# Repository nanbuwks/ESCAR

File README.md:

# ESCAR

ESP8266 IoT prototype board.

function:

- LEGO block 8 x 4 knoch size
- DC motor driver x 2
- Universal Area
- 5V to 3.3V regulator
- Full color LED
- Serial connector

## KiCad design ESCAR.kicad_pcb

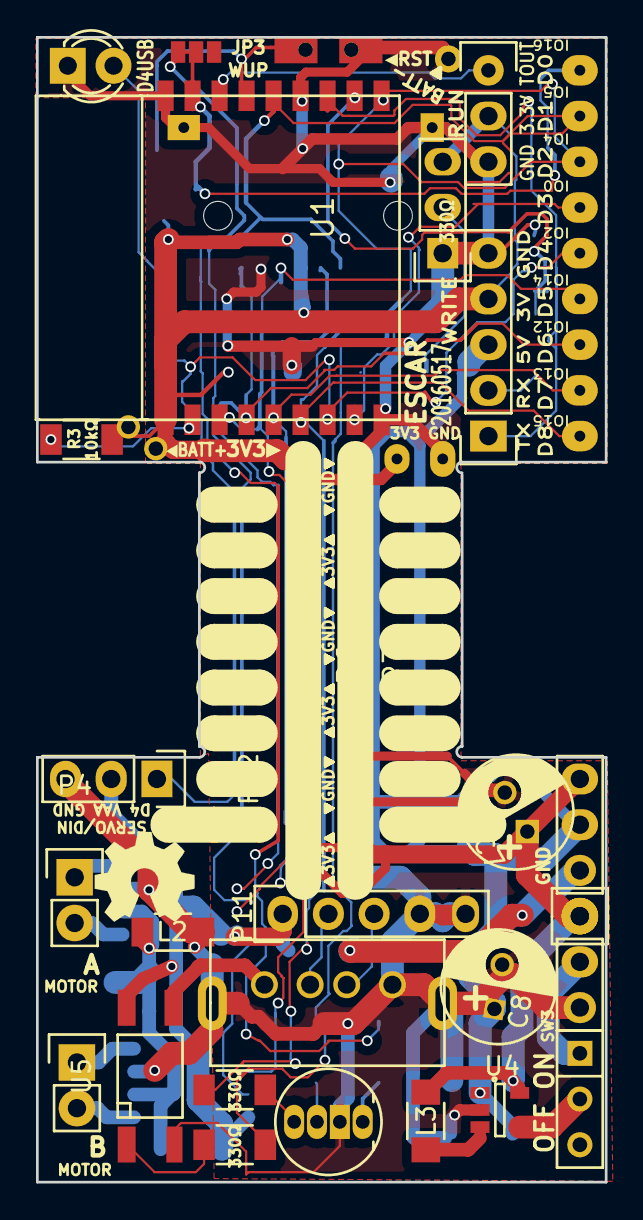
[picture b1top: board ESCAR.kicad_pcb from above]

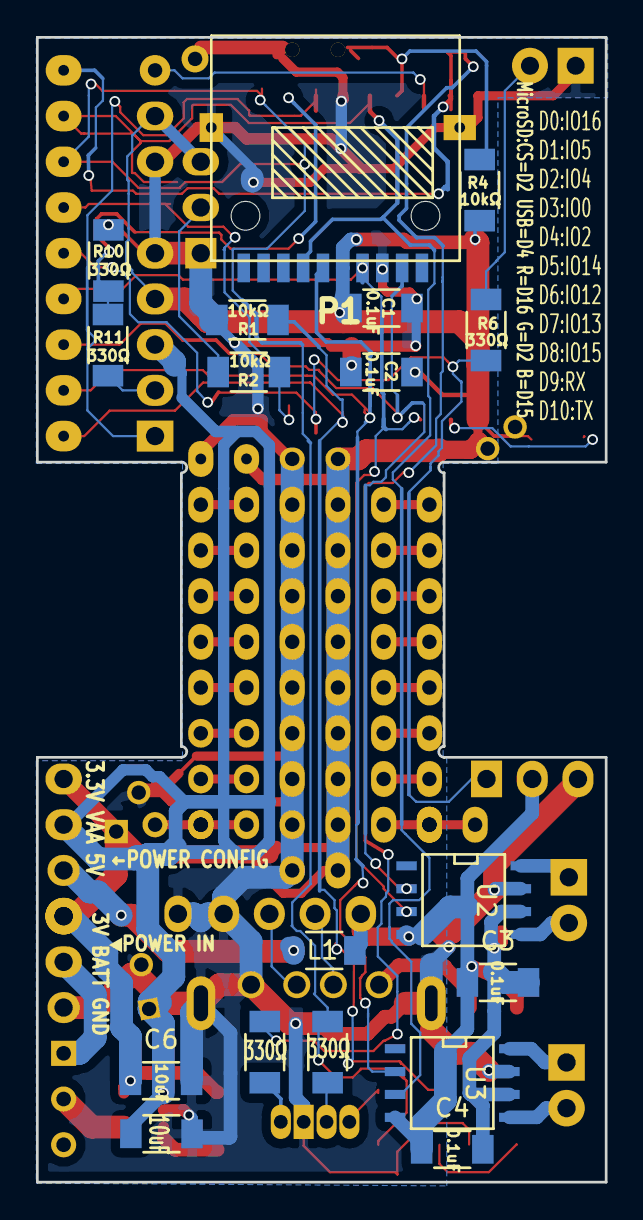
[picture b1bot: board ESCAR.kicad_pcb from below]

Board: 2 copper layers, 31.6 x 63.6 mm, 69 parts (36 on the bottom side), 37 nets.

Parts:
C1, C2, C3, C4: 0.1uF; C_1206_HandSoldering_Small
C5, C6: 10uF; C_1206_HandSoldering_Small
C7, C8: 100uF; C_Radial_D6.3_L11.2_P2.5
D1: YELLOW; LED-3MM
D2: LED_RCBG; LED-RGB-5MM_Common_Cathode
JP1: MODE_JP; Pin_Header_Straight_1x03
JP2: WAKEUP; Solder_Jumper_3
JP4: POWER_JUMPER; Pin_Header_Straight_1x04
L1, L2: INDUCTOR_SMALL; C_1206_HandSoldering_Small
L3: 4.7uH; C_1206_HandSoldering_Small
OSHW: 1.1; OSHW_LOGL_SYLK_5mm
P1: MICRO_SD; TF_Socket_DONGGUAN_MINYUE_ELECTRONICS
P2: BREADBOARD; SolderWirePad_Oval_9xInline_0-6mmDrill
P3: PROGRAM; Pin_Header_Straight_1x05
P4: MOTOR_A; Pin_Header_Straight_1x02
P5: MOTOR_B; Pin_Header_Straight_1x02
P6, P7: CONN_01X10; Padmatrix-wide-01x10
P8: POWER_IN; Pin_Header_Straight_1x03
P9: UNIVERSAL PAD; Padmatrix-wide-02x01
P9#2, P9#3, P9#4, P9#5, P9#6, P9#7, P9#8, P9#9, P9#10, P9#11, P9#12, P9#13, P9#14, P9#15, P9#16, P9#17, P9#18: UNIVERSAL_PAD; Padmatrix-wide-02x01
P10: USB_A; USB_A_Vertical_Short
P11: USB_B; Pin_Header_Straight_1x05
P12: SERVO/INPUT; Pin_Header_Straight_1x03
P13: ANALOG; Pin_Header_Straight_1x03
P14, P14#2: BATTERY3.3V; SolderWirePad_single_0-8mmDrill
P15: BATTERYGND; SolderWirePad_single_0-8mmDrill
P16: BREADBOARD_POWER; Padmatrix-wide-02x01
R1, R2, R3, R4: 10kΩ; R_1206_HandSoldering_Small
R6, R7, R8, R9, R10, R11, R12: 330Ω; R_1206_HandSoldering_Small
SW1: RESET; SW_SMD_3x6_WithHole
SW3: POWER_SW; SW_Micro_SPST
U1: ESP-WROOM-02; ESP_WROOM_02
U2, U3: TC117HS; SOIC-8-N
U4: MT5201-3.3N; SOT-23-5
U5: TLP222A; Optocoupler_SMD_HandSoldering_KPC357_LTV35x_PC357_SingleCha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

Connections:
+3V3: C1.1, C2.1, C6.1, C7.1, JP1.3, JP4.1, JP4.4, L3.2, P1.4, P3.4, P6.1, P6.2, P6.3, P6.4, P6.5, P6.6, P6.7, P6.8, P6.9, P6.10, P8.1, P13.2, P14.1, P14#2.1, P16.1, R3.2, R4.2, U1.1, U4.5
+5V: C5.1, C8.1, JP4.3, P3.3, SW3.2, U4.1, U4.4
+BATT: P8.2, SW3.1
GND: C1.2, C2.2, C5.2, C6.2, C7.2, C8.2, D1.1, D2.2, JP1.1, L2.2, P1.6, P3.5, P7.1, P7.2, P7.3, P7.4, P7.5, P7.6, P7.7, P7.8, P7.9, P7.10, P8.3, P10.4, P10.5, P11.4, P11.5, P12.3, P13.3, P15.1, P16.2, R1.1, R10.1, SW1.1, U1.9, U1.13, U1.18, U2.7, U3.7, U4.2, U5.2
unnamed: C3.2, C4.2, L2.1, U2.6, U3.6
unnamed: D1.2, R6.1
unnamed: D2.1, R9.1
unnamed: D2.3, R7.1
unnamed: D2.4, R8.1
unnamed: JP1.2, R2.1
unnamed: JP2.1, R4.1, SW1.2, U1.15
unnamed: JP2.2, JP2.3, P2.1, R9.2, U1.17
unnamed: JP4.2, L1.1
unnamed: L3.1, U4.3
unnamed: P1.2, P2.2, U1.14, U3.3
unnamed: P1.3, P2.8, U1.5, U3.2
unnamed: P1.5, P2.6, U1.3, U2.3
unnamed: P1.7, P2.7, U1.4, U2.2
unnamed: P2.3, R7.2, R12.1, U1.10
unnamed: P2.4, R2.2, U1.8
unnamed: P2.9, R1.2, R8.2, U1.6
unnamed: P3.1, U1.12
unnamed: P3.2, R11.1
unnamed: P4.1, U2.8
unnamed: P4.2, U2.5
unnamed: P5.1, U3.8
unnamed: P5.2, U3.5
unnamed: P9.1, P9.2, P9#2.1, P9#2.2, P9#3.1, P9#3.2, P9#4.1, P9#4.2, P9#5.1, P9#5.2, P9#6.1, P9#6.2, P9#7.1, P9#7.2, P9#8.1, P9#8.2, P9#9.1, P9#9.2, P9#10.1, P9#10.2, P9#11.1, P9#11.2, P9#12.1, P9#12.2, P9#13.1, P9#13.2, P9#14.1, P9#14.2, P9#15.1, P9#15.2, P9#16.1, P9#16.2, P9#17.1, P9#17.2, P9#18.1, P9#18.2
unnamed: P10.1, U5.3
unnamed: P10.2, P11.2
unnamed: P10.3, P11.3
unnamed: P2.5, P12.1, R6.2, U1.7
unnamed: P13.1, U1.16
unnamed: R3.1, U1.2
unnamed: R10.2, R11.2, U1.11
unnamed: R12.2, U5.1
VAA: C3.1, C4.1, L1.2, P11.1, P12.2, U2.4, U3.4, U5.4

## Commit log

2016-04-17 First files
2016-04-17 add KiCad Files
2016-04-17 file rename ESPAR -> ESCAR
2016-05-09 add dividing resisters for RX pin , and organized many point.
2016-06-17 Ver20160517 Release. Add USB switch function, change GPIO assign.
2016-07-11 Ver20160617 Release. change PORT mapping, pin header hole size, silk. and few bug fix
